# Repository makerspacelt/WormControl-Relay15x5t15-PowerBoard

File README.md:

---

WormControl Relay PowerBoard

NOTE: This is only a prototype now, so things might not work and everything might change 

Basic target features:

* Compatibility with esphome and Home Assistant

Dev NOTE: before commit, run `./kibot.sh` to regenerate documentation, bom, gerbers and other assets.

* [schematics.pdf](gen/schematics.pdf)
* [pcb.pdf with dimensions](gen/pcb.pdf)
* [ibom.html](gen/single/ibom.html)

---

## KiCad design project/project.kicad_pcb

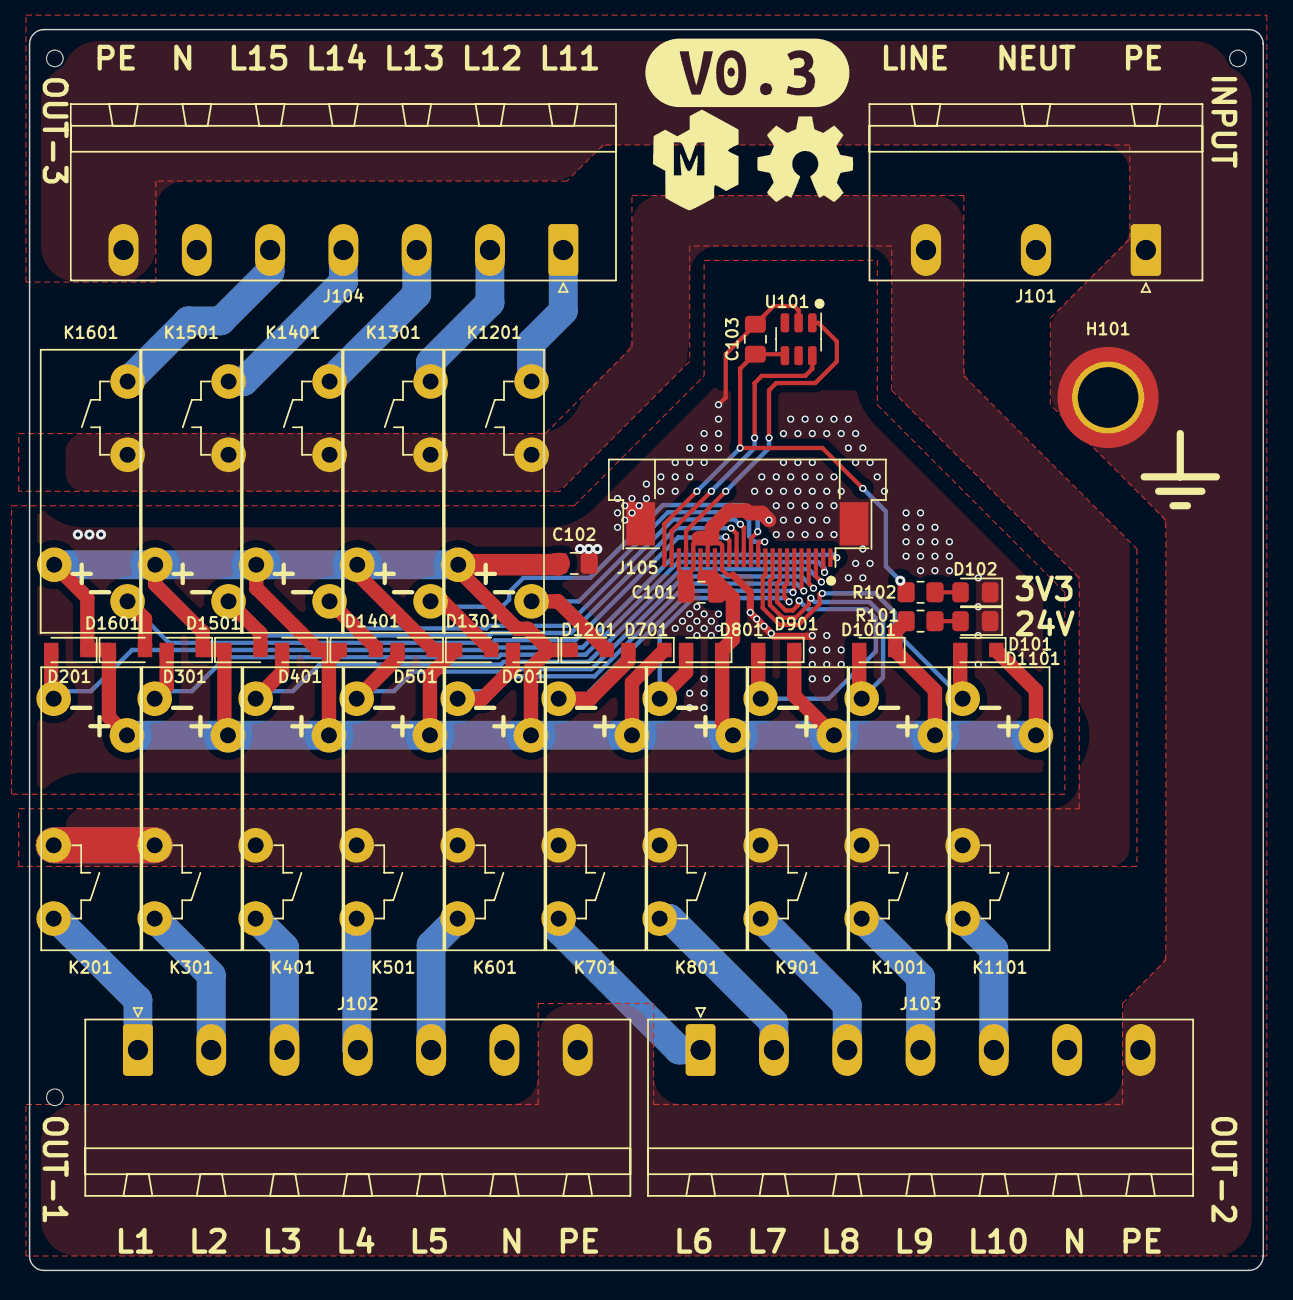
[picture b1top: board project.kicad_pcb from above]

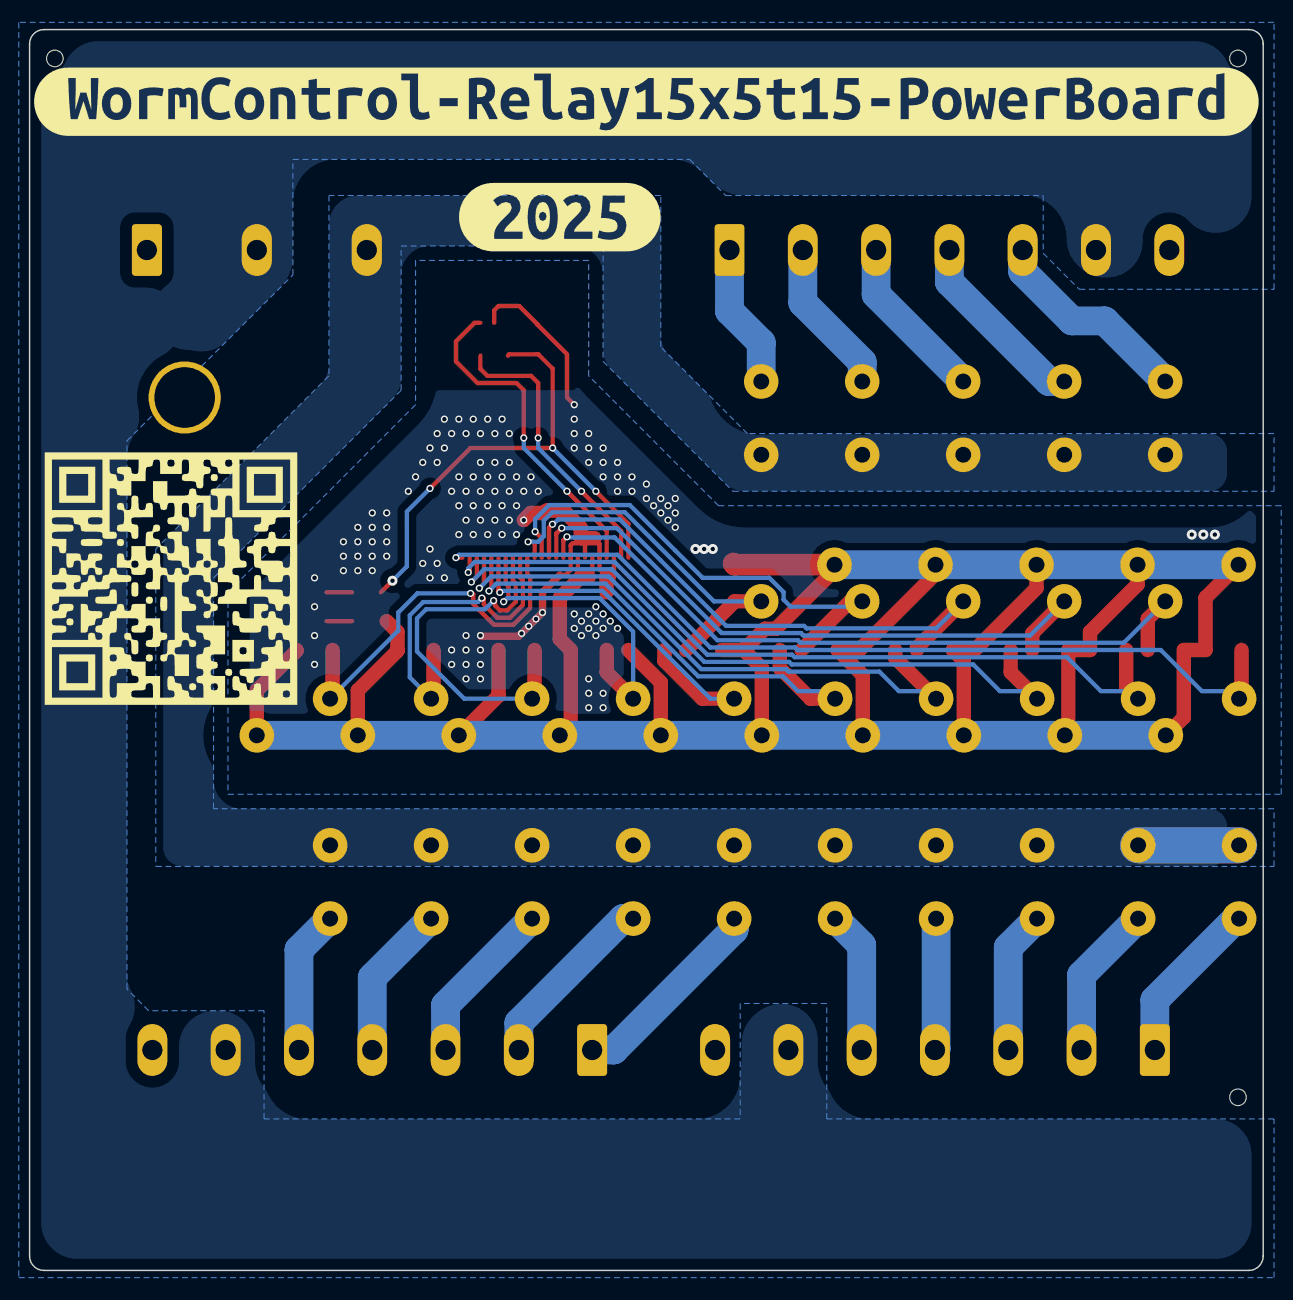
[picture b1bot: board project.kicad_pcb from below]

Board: 2 copper layers, 85.5 x 86.0 mm, 49 parts (2 on the bottom side), 40 nets.

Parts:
C101: 10u/50v; C_0805_2012Metric_Pad1.18x1.45mm_HandSolder
C102, C103: 100n; C_0805_2012Metric_Pad1.18x1.45mm_HandSolder
D101, D102: GREEN; LED_0805_2012Metric_Pad1.15x1.40mm_HandSolder
D201, D301, D401, D501, D601, D701, D801, D901, D1001, D1101, D1201, D1301, D1401, D1501, D1601: B5819WS; D_SOD-323_HandSoldering
G101: Logo_Open_Hardware_Large; OSHW-Symbol_6.7x6mm_SilkScreen
G102: LOGO_KMS; logo_kms_small_silkscreen
H101: M3; post_m3x5mm
J101: IN; PhoenixContact_GMSTBA_2,5_3-G-7,62_1x03_P7.62mm_Horizontal
J102, J103, J104: 1x7_5.08; PhoenixContact_MSTBA_2,5_7-G-5,08_1x07_P5.08mm_Horizontal
J105: FFC Connector; AFC07-S24FCC-00
K201, K301, K401, K501, K601, K701, K801, K901, K1001, K1101, K1201, K1301, K1401, K1501, K1601: P6D-04P
R101: 47k; R_0805_2012Metric_Pad1.20x1.40mm_HandSolder
R102: 4k7; R_0805_2012Metric_Pad1.20x1.40mm_HandSolder
U101: GX101; SOT-23-6
kibuzzard-68EEE57B: G***; kibuzzard-68EEE57B
kibuzzard-6750F085: G***; kibuzzard-6750F085
kibuzzard-6798B3C4: G***; kibuzzard-6798B3C4

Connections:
+3V3: C103.1, J105.24, R102.1, U101.4 (V+)
+24V: C101.1, C102.1, D201.1 (K), D301.1 (K), D401.1 (K), D501.1 (K), D601.1 (K), D701.1 (K), D801.1 (K), D901.1 (K), D1001.1 (K), D1101.1 (K), D1201.1 (K), D1301.1 (K), D1401.1 (K), D1501.1 (K), D1601.1 (K), J105.17, J105.19, K201.13, K301.13, K401.13, K501.13, K601.13, K701.13, K801.13, K901.13, K1001.13, K1101.13, K1201.13, K1301.13, K1401.13, K1501.13, K1601.13, R101.1
/_relay2/COM: J102.1, K201.7
/_relay2/EN: D201.2 (A), J105.1, K201.1
/_relay3/COM: J102.2, K301.7
/_relay3/EN: D301.2 (A), J105.2, K301.1
/_relay4/COM: J102.3, K401.7
/_relay4/EN: D401.2 (A), J105.3, K401.1
/_relay5/COM: J102.4, K501.7
/_relay5/EN: D501.2 (A), J105.4, K501.1
/_relay6/COM: J102.5, K601.7
/_relay6/EN: D601.2 (A), J105.5, K601.1
/_relay7/COM: J103.1, K701.7
/_relay7/EN: D701.2 (A), J105.6, K701.1
/_relay8/COM: J103.2, K801.7
/_relay8/EN: D801.2 (A), J105.7, K801.1
/_relay9/COM: J103.3, K901.7
/_relay9/EN: D901.2 (A), J105.8, K901.1
/_relay10/COM: J103.4, K1001.7
/_relay10/EN: D1001.2 (A), J105.9, K1001.1
/_relay11/COM: J103.5, K1101.7
/_relay11/EN: D1101.2 (A), J105.10, K1101.1
/_relay12/COM: J104.1, K1201.7
/_relay12/EN: D1201.2 (A), J105.11, K1201.1
/_relay13/COM: J104.2, K1301.7
/_relay13/EN: D1301.2 (A), J105.12, K1301.1
/_relay14/COM: J104.3, K1401.7
/_relay14/EN: D1401.2 (A), J105.13, K1401.1
/_relay15/COM: J104.4, K1501.7
/_relay15/EN: D1501.2 (A), J105.14, K1501.1
/_relay16/COM: J104.5, K1601.7
/_relay16/EN: D1601.2 (A), J105.15, K1601.1
GND: C101.2, C102.2, C103.2, D101.1 (K), D102.1 (K), J105.16, J105.18, J105.20, J105.22, J105.MP (MountPin), U101.2 (GND)
GNDPWR: H101.1, J101.1, J102.7, J103.7, J104.7
LINE: J101.3, K201.5, K301.5, K401.5, K501.5, K601.5, K701.5, K801.5, K901.5, K1001.5, K1101.5, K1201.5, K1301.5, K1401.5, K1501.5, K1601.5
NEUT: J101.2, J102.6, J103.6, J104.6
unnamed: D101.2 (A), R101.2
unnamed: D102.2 (A), R102.2
SCL: J105.21, U101.1 (SCL)
SDA: J105.23, U101.6 (SDA)

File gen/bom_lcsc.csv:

"Quantity","LCSC Part Number","Value","Footprint"
"1","C440891","1x3 screw plug",""
"3","C409127","1x7 screw plug",""
"1","C7543499","FFC Cable",""
"2","C28233","100n","C_0805_2012Metric_Pad1.18x1.45mm_HandSolder"
"1","C440198","10u/50v","C_0805_2012Metric_Pad1.18x1.45mm_HandSolder"
"15","C402231","B5819WS","D_SOD-323_HandSoldering"
"2","C2297","GREEN","LED_0805_2012Metric_Pad1.15x1.40mm_HandSolder"
"1","C2915636","M3","post_m3x5mm"
"3","C46179","1x7_5.08","PhoenixContact_MSTBA_2,5_7-G-5,08_1x07_P5.08mm_Horizontal"
"1","C11057","FFC Connector","AFC07-S24FCC-00"
"1","C441247","IN","PhoenixContact_GMSTBA_2,5_3-G-7,62_1x03_P7.62mm_Horizontal"
"15","C1524870","P6D-04P","P6D-04P"
"1","C17673","4k7","R_0805_2012Metric_Pad1.20x1.40mm_HandSolder"
"1","C17713","47k","R_0805_2012Metric_Pad1.20x1.40mm_HandSolder"
"1","C5441728","GX101","SOT-23-6"

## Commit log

2024-12-05 initial project
2024-12-19 removing fets as driving is upstairs now
2024-12-20 fixing stencil for post footprint
2025-01-07 pcb resize, 3d models, inset connectors, gerbers format
2025-01-07 removing dates from gerbers
2025-01-28 bumping up version to v0.2
2025-10-15 replacing FFC connector
